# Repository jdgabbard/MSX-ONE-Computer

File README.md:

# MSX-ONE Computer

A small, easy to build MSX1 compatible computer.<br>

***See Build Notes file for special instructions!***

Designed as a cheap, and easy to build, MSX1 computer for the US Vintage Computer enthusiast.

**Features include:**<br><br>
-Small Footprint:
     -Mainboard size: 200mm x 150mm
     -Keyboard size: 200mm x 95mm
-Power-On Reset Supervisor Circuit providing automatic 200ms Reset.
-Flexible power input handles +12v DC to +12v AC power supplies.<br>
-Implements +12v/-12v rails, so Audio Cartridges work correctly.<br>
-2x Sega Gamepad compatible ports, since finding MSX controllers in the US is all but impossible.<br>
-TMS9118 Low Cost alternative does away with numerous DRAM chips, or finicky SRAM circuits, using just two 4bit DRAMs.<br>
-Two Primary Slots available to the user.<br>
-Construction consisting of off the shelf TTL logic, without the need for any programable logic, SPLDs or FPGAs to worry about programming.<br>
-A small form factor, consisting of a PCB approximately the same size as a ZX Spectrum: 200mm x 150mm<br>
-A stackable keyboard (Omega Home Computer Compatible) using cheap tactile switches with an optional cover for aesthetics.<br><br>

**Inspiration**
This computer was heavily inspired by, and borrowing from, both Sergey Kiselev's Omega Home Computer, and the JFF Computer (https://github.com/konkotgit/JFF), as well as the Casio MX-10.<br><br>

I desired a MSX without all the fluff, but with the modularity that the Omega Computer affords.  I wanted a simplified circuit, but with nice options such as power regulation, options for a mechanical power switch, and +12v/-12v rails.  The MSX-ONE gives the casual MSX user just the basics to have a functional yet flexible machine for playing MSX1 games.  And it does this without the need for programmable logic.  The design uses all off the shelf TTL compatible parts, which are still in current production.<br><br>

**Specifications:**<br>
-TMS9118 VDP with 16k DRAM (2x4bit DRAMS)<br>
-32k EEPROM in SLOT0 (BIOS with International Keyboard, Mapper Initializer & BASIC 1.0)<br>
-64K SRAM in SLOT3<br>
-Standard PSG<br>
-International Keyboard<br>
-No Printer Port<br>
-No Cassette Interface<br>
-No Disk Drive<br>
-No Fluff<br>

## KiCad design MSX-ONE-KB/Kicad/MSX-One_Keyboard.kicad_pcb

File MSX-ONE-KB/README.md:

# MSX-ONE Keyboard

The keyboard circuit is completely working, and stands at vesion 1.0

I will likely add a different board layout using standard 1/4w resistors for the LEDs.

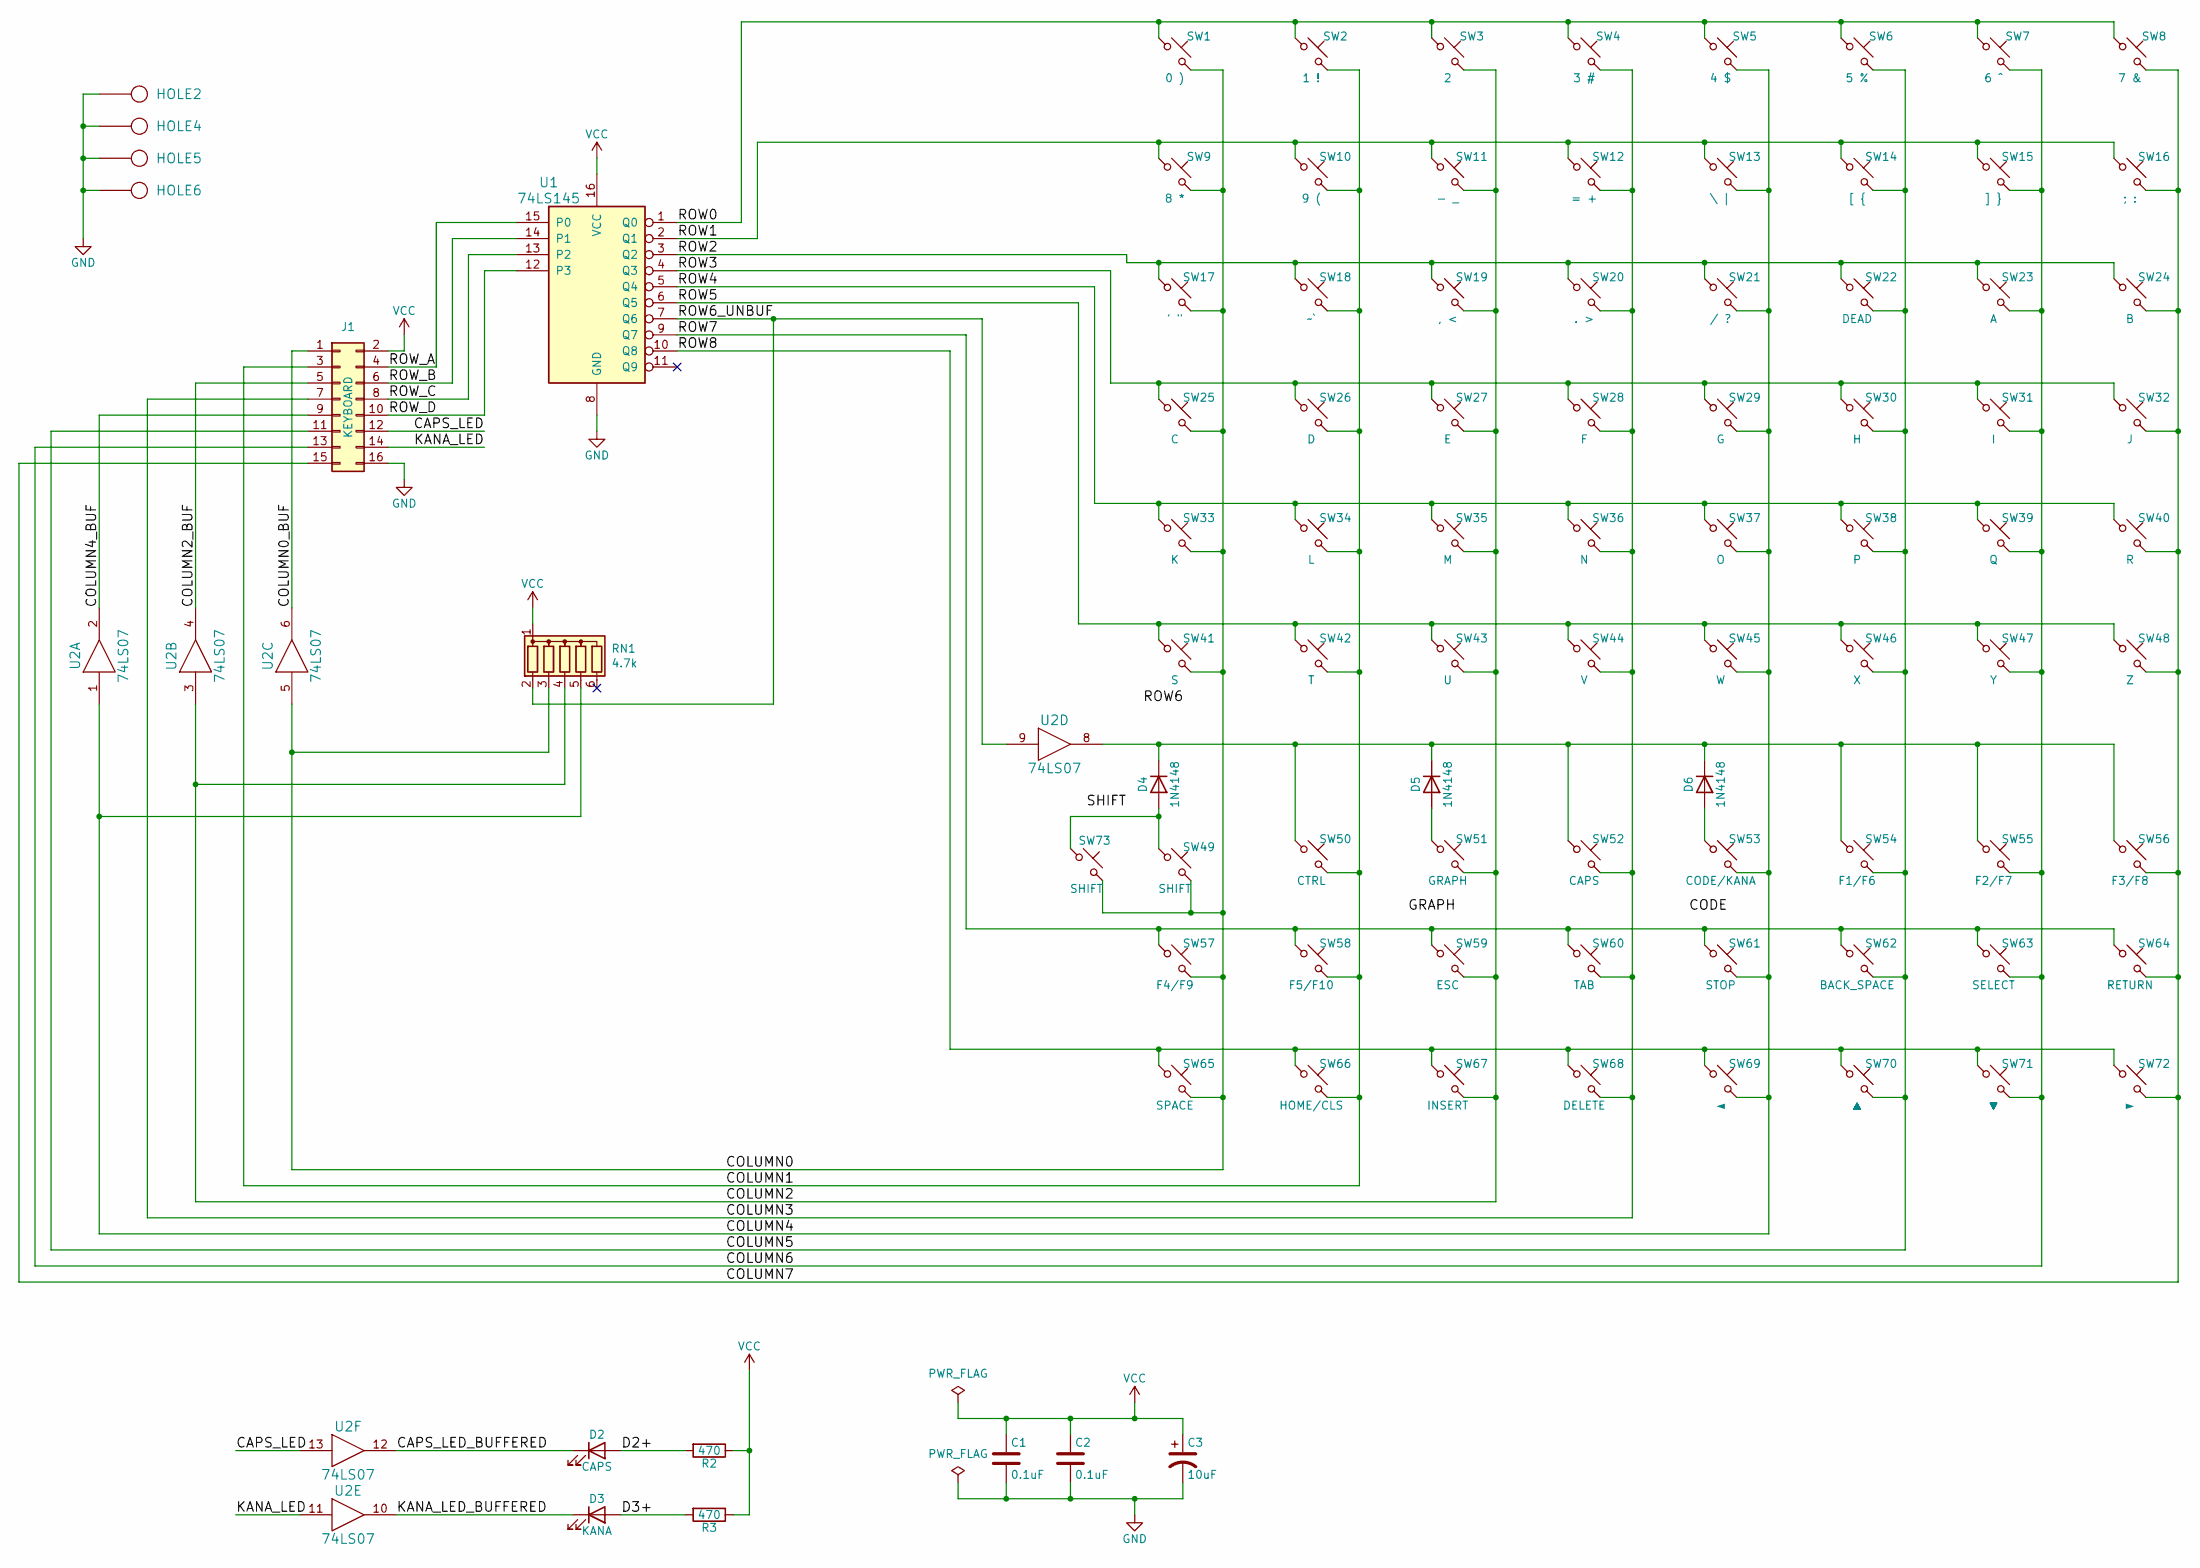
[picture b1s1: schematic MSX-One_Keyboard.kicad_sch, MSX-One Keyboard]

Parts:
C1, C2: 0.1uF; C_0805_2012Metric_Pad1.18x1.45mm_HandSolder
C3: 10uF; CP_Elec_4x5.7
D2: CAPS; LED_D3.0mm
D3: KANA; LED_D3.0mm
D4, D5, D6: 1N4148; D_DO-35_SOD27_P7.62mm_Horizontal
HOLE2, HOLE4, HOLE5, HOLE6: HOLE; Hole_3mm
J1: KEYBOARD; IDC-Header_2x08_P2.54mm_Horizontal
R2, R3: 470; R_0805_2012Metric_Pad1.20x1.40mm_HandSolder
RN1: 4.7k; Conn_SIL6
SW1: 0 ); SW_PUSH_6mm_H8mm
SW2: 1 !; SW_PUSH_6mm_H8mm
SW3: 2; SW_PUSH_6mm_H8mm
SW4: 3 #; SW_PUSH_6mm_H8mm
SW5: 4 $; SW_PUSH_6mm_H8mm
SW6: 5 %; SW_PUSH_6mm_H8mm
SW7: 6 ^; SW_PUSH_6mm_H8mm
SW8: 7 &; SW_PUSH_6mm_H8mm
SW9: 8 *; SW_PUSH_6mm_H8mm
SW10: 9 (; SW_PUSH_6mm_H8mm
SW11: - _; SW_PUSH_6mm_H8mm
SW12: = +; SW_PUSH_6mm_H8mm
SW13: \ |; SW_PUSH_6mm_H8mm
SW14: [ {; SW_PUSH_6mm_H8mm
SW15: ] }; SW_PUSH_6mm_H8mm
SW16: ; :; SW_PUSH_6mm_H8mm
SW17: ' "; SW_PUSH_6mm_H8mm
SW18: ~`; SW_PUSH_6mm_H8mm
SW19: , <; SW_PUSH_6mm_H8mm
SW20: . >; SW_PUSH_6mm_H8mm
SW21: / ?; SW_PUSH_6mm_H8mm
SW22: DEAD; SW_PUSH_6mm_H8mm
SW23: A; SW_PUSH_6mm_H8mm
SW24: B; SW_PUSH_6mm_H8mm
SW25: C; SW_PUSH_6mm_H8mm
SW26: D; SW_PUSH_6mm_H8mm
SW27: E; SW_PUSH_6mm_H8mm
SW28: F; SW_PUSH_6mm_H8mm
SW29: G; SW_PUSH_6mm_H8mm
SW30: H; SW_PUSH_6mm_H8mm
SW31: I; SW_PUSH_6mm_H8mm
SW32: J; SW_PUSH_6mm_H8mm
SW33: K; SW_PUSH_6mm_H8mm
SW34: L; SW_PUSH_6mm_H8mm
SW35: M; SW_PUSH_6mm_H8mm
SW36: N; SW_PUSH_6mm_H8mm
SW37: O; SW_PUSH_6mm_H8mm
SW38: P; SW_PUSH_6mm_H8mm
SW39: Q; SW_PUSH_6mm_H8mm
SW40: R; SW_PUSH_6mm_H8mm
SW41: S; SW_PUSH_6mm_H8mm
SW42: T; SW_PUSH_6mm_H8mm
SW43: U; SW_PUSH_6mm_H8mm
SW44: V; SW_PUSH_6mm_H8mm
SW45: W; SW_PUSH_6mm_H8mm
SW46: X; SW_PUSH_6mm_H8mm
SW47: Y; SW_PUSH_6mm_H8mm
SW48: Z; SW_PUSH_6mm_H8mm
SW49, SW73: SHIFT; SW_PUSH_6mm_H8mm
SW50: CTRL; SW_PUSH_6mm_H8mm
SW51: GRAPH; SW_PUSH_6mm_H8mm
SW52: CAPS; SW_PUSH_6mm_H8mm
SW53: CODE/KANA; SW_PUSH_6mm_H8mm
SW54: F1/F6; SW_PUSH_6mm_H8mm
SW55: F2/F7; SW_PUSH_6mm_H8mm
SW56: F3/F8; SW_PUSH_6mm_H8mm
SW57: F4/F9; SW_PUSH_6mm_H8mm
SW58: F5/F10; SW_PUSH_6mm_H8mm
SW59: ESC; SW_PUSH_6mm_H8mm
SW60: TAB; SW_PUSH_6mm_H8mm
SW61: STOP; SW_PUSH_6mm_H8mm
SW62: BACK_SPACE; SW_PUSH_6mm_H8mm
SW63: SELECT; SW_PUSH_6mm_H8mm
SW64: RETURN; SW_PUSH_6mm_H8mm
SW65: SPACE; SW_PUSH_6mm_H8mm
SW66: HOME/CLS; SW_PUSH_6mm_H8mm
SW67: INSERT; SW_PUSH_6mm_H8mm
SW68: DELETE; SW_PUSH_6mm_H8mm
SW69: ◄; SW_PUSH_6mm_H8mm
SW70: ▲; SW_PUSH_6mm_H8mm
SW71: ▼; SW_PUSH_6mm_H8mm
SW72: ►; SW_PUSH_6mm_H8mm
U1: 74LS145; SOIC-16_3.9x9.9mm_P1.27mm
U2: 74LS07; SOIC-14_3.9x8.7mm_P1.27mm

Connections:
/CAPS_LED: J1.12, U2.13
/CAPS_LED_BUFFERED: D2.1 (K), U2.12
/COLUMN0: RN1.3 (R2), SW1.2, SW9.2, SW17.2, SW25.2, SW33.2, SW41.2, SW49.2, SW57.2, SW65.2, SW73.2, U2.5
/COLUMN0_BUF: J1.1, U2.6
/COLUMN1: J1.3, SW2.2, SW10.2, SW18.2, SW26.2, SW34.2, SW42.2, SW50.2, SW58.2, SW66.2
/COLUMN2: RN1.4 (R3), SW3.2, SW11.2, SW19.2, SW27.2, SW35.2, SW43.2, SW51.2, SW59.2, SW67.2, U2.3
/COLUMN2_BUF: J1.5, U2.4
/COLUMN3: J1.7, SW4.2, SW12.2, SW20.2, SW28.2, SW36.2, SW44.2, SW52.2, SW60.2, SW68.2
/COLUMN4: RN1.5 (R4), SW5.2, SW13.2, SW21.2, SW29.2, SW37.2, SW45.2, SW53.2, SW61.2, SW69.2, U2.1
/COLUMN4_BUF: J1.9, U2.2
/COLUMN5: J1.11, SW6.2, SW14.2, SW22.2, SW30.2, SW38.2, SW46.2, SW54.2, SW62.2, SW70.2
/COLUMN6: J1.13, SW7.2, SW15.2, SW23.2, SW31.2, SW39.2, SW47.2, SW55.2, SW63.2, SW71.2
/COLUMN7: J1.15, SW8.2, SW16.2, SW24.2, SW32.2, SW40.2, SW48.2, SW56.2, SW64.2, SW72.2
/D2+: D2.2 (A), R2.2
/D3+: D3.2 (A), R3.2
/KANA_LED: J1.14, U2.11
/KANA_LED_BUFFERED: D3.1 (K), U2.10
/ROW0: SW1.1, SW2.1, SW3.1, SW4.1, SW5.1, SW6.1, SW7.1, SW8.1, U1.1 (Q0)
/ROW1: SW9.1, SW10.1, SW11.1, SW12.1, SW13.1, SW14.1, SW15.1, SW16.1, U1.2 (Q1)
/ROW2: SW17.1, SW18.1, SW19.1, SW20.1, SW21.1, SW22.1, SW23.1, SW24.1, U1.3 (Q2)
/ROW3: SW25.1, SW26.1, SW27.1, SW28.1, SW29.1, SW30.1, SW31.1, SW32.1, U1.4 (Q3)
/ROW4: SW33.1, SW34.1, SW35.1, SW36.1, SW37.1, SW38.1, SW39.1, SW40.1, U1.5 (Q4)
/ROW5: SW41.1, SW42.1, SW43.1, SW44.1, SW45.1, SW46.1, SW47.1, SW48.1, U1.6 (Q5)
/ROW6_UNBUF: RN1.2 (R1), U1.7 (Q6), U2.9
/ROW7: SW57.1, SW58.1, SW59.1, SW60.1, SW61.1, SW62.1, SW63.1, SW64.1, U1.9 (Q7)
/ROW8: SW65.1, SW66.1, SW67.1, SW68.1, SW69.1, SW70.1, SW71.1, SW72.1, U1.10 (Q8)
/ROW_A: J1.4, U1.15 (P0)
/ROW_B: J1.6, U1.14 (P1)
/ROW_C: J1.8, U1.13 (P2)
/ROW_D: J1.10, U1.12 (P3)
GND: C1.2, C2.2, C3.2, HOLE2.1, HOLE4.1, HOLE5.1, HOLE6.1, J1.16, U1.8 (GND), U2.7 (GND)
unnamed: D4.1 (K), D5.1 (K), D6.1 (K), SW50.1, SW52.1, SW54.1, SW55.1, SW56.1, U2.8
unnamed: D4.2 (A), SW49.1, SW73.1
unnamed: D5.2 (A), SW51.1
unnamed: D6.2 (A), SW53.1
VCC: C1.1, C2.1, C3.1, J1.2, R2.1, R3.1, RN1.1 (common), U1.16 (VCC), U2.14 (VCC)

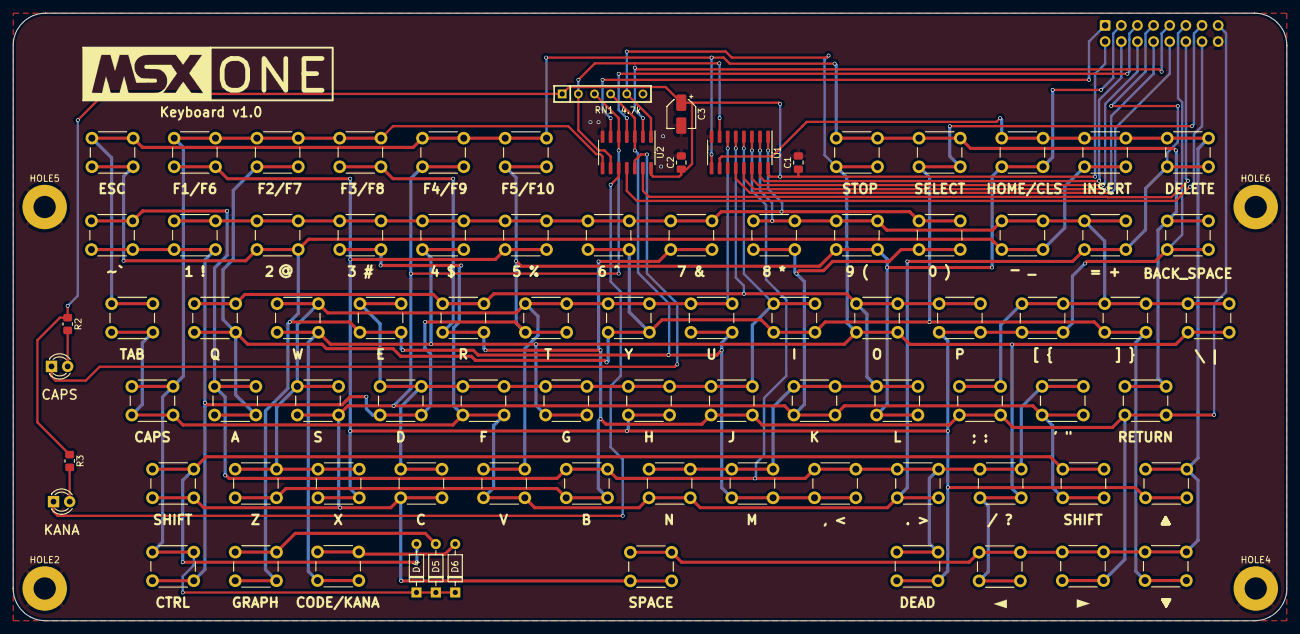
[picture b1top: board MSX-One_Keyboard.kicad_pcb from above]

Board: 2 copper layers, 200.3 x 95.6 mm, 91 parts (1 on the bottom side), 36 nets.

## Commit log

2025-02-15 Initial Upload
    Initial upload of project to GitHub.
2025-02-15 Update README.md
    Added Render of MSX-ONE
2025-02-15 MAX701 Information
    Provided info on the MAX701 circuit.
2025-02-15 Update MAX701
2025-02-15 Removed unneeded items.
2025-02-17 Update Build_Notes.md
    Added partial BOM
2025-02-18 Updated Build Notes
2025-02-18 BOM Update
    BOM Update with minor change to PCB for parts availability.
